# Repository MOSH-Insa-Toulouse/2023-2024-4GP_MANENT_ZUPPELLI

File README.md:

# 2023-2024-4GP_MANENT_ZUPPELLI
--- 
## Sommaire
   - [I) Contexte et objectifs du projet](#I-Contexteetobjectifsduprojet)
   - [II) Capteur à jauge de contrainte à base de crayon graphite](#II-Capteuràjaugedecontrainteàbasedecrayongraphite)
   - [III) Partie Analogique](#III-PartieAnalogique)
   - [IV) Code Arduino](#IV-CodeArduino)
   - [V) KiCad](#V-KiCad)
   - [VI) Banc de tests](#VI-Bancdetests)
   - [VII) Application mobile](#VII-Applicationmobile)
   - [VIII) Datasheet](#VIII-Datasheet)
     
---
  
## I) Contexte et objectifs du projet

L'objectif de ce projet est de réaliser un capteur low-tech à base de graphite. Les recherches ont démontré les nombreux avantages du carbone graphite. L’électronique à base de papier gagne en popularité parmi les ingénieurs grâce à sa facilité d’approvisionnement, sa simplicité de fabrication et son faible coût.<br>
Nous avons dû réaliser tous les processus de fabrication d'un shield PCB. Nous l'avons ensuite connecté à une plaque Arduino UNO.<br>
Notre shield contient 6 composants différents : une jauge de contrainte, un flex sensor, un écran oled, un encodeur rotatoire, un potentiomètre digital et un module Bluetooth.<br>
Par ailleurs, la carte Arduino fonctionne avec un code.<br>
Nous avons ensuite réalisé une application mobile connectée au module bluetooth.<br>
Nous avons évalué le capteur sur un banc de test.<br>
Puis nous avons fini par réaliser la datasheet du capteur de contrainte.<br>

## II)Capteur à jauge de contrainte à base de crayon graphite

Ce capteur low-tech utilise la théorie de la percolation au sein d’un système granulaire constitué de nanoparticules de graphite.<br>
Nous déposons une fine couche de graphite sur la feuille de papier ce qui présente un réseau percolé caractéristique. Dans ce réseau, le transport des électrons entre les nanoparticules est basé sur le mécanisme de l’effet tunnel.<br>
Lors de l'application d'une tension, le réseau percolé se trouve directement étendu. Cette déformation entraîne une augmentation de la distance effective entre les particules de graphite au sein du réseau. Une partie des chemins de percolation sont par conséquent rompus. Ainsi, la conduction du matériau diminue, donc la résistance de la couche de graphite augmente.<br>
Inversement, lors de l’application de déformations en compression, le réseau percolé se trouve directement comprimé. Cette déformation entraîne une diminution de la distance effective entre les particules.<br> Ainsi, de nouveaux chemins de percolation sont créés, la conduction du matériau augmente, soit la résistance de la couche de graphite diminue.

Une jauge de contrainte est un circuit résistif dont la résistance varie en fonction de sa déformation. Donc en mesurant les variations de résistance de la jauge, nous en avons déduit la contrainte et la déformation appliquées.<br>
Notre jauge de contrainte est alimentée par une tension régulée de 5V d'une carte Arduino UNO.
<br>
Ci-dessous, les 4 différentes jauges de contrainte que nous avons utilisé dans ce projet.

<p align="center">

<br>
<i>Capteur à jauge de contrainte à base de crayon graphite</i>
</p>

## III) Partie Analogique

Ce capteur graphite possède une résistance variable de l'ordre du GΩ. Le courant généré lorsque l'on applique une tension de 5V aux bornes du capteur est très faible.<br>
Pour obtenir un signal exploitable nous avons dû l'amplifier. Pour ce faire, nous avons utilisé un montage transimpédance constitué d'un amplificateur opérationnel.<br>
Pour cela nous avons dans un premier temps effectué une simulation électronique du capteur et de ce montage transimpédance sous LTSpice. Voici ci-dessous le montage réalisé sous LTSpice. Pour notre montage nous avons choisi l'AOP LTC1050 prenant en entrée un courant faible (de l'ordre d'une dizaine de picoampère).

<p align="center">

<br>
<i>Circuit amplificateur réalisé dans LTSpice</i>
</p>
<br>
Ce circuit amplificateur contient également 3 filtres passe bas passifs, dont nous avons pu tester le bon fonctionnement alternativement.<br>
<br>
- Le premier étage a une fréquence de coupure de 16 Hz, il permet de filtrer les bruits du courant en entrée. Nous avons testé ce premier étage pour vérifier que la fréquence de coupure soit la bonne.
<br>
</p>
<p align="center">

<br>
<i>Simulation de l'étage 1 dans LTSpice</i>
</p>
En effet la fréquence de coupure est la bonne.
<br>
- Le second étage a une fréquence de coupure de 1,6 Hz. Il permet de filtrer la composante de bruit du réseau électrique: le bruit à 50 Hz.
<br>
</p>
<p align="center">

<br>
<i>Simulation de l'étage 2 dans LTSpice</i>
</p>
En effet la fréquence de coupure est la bonne.
<br>
- Le dernier étage a une fréquence de coupure à 1,6 kHz qui permet d'atténuer le bruit provenant lors du traitement électronique.
<br>
</p>
<p align="center">

<br>
<i>Simulation de l'étage 3 dans LTSpice</i>
</p>
En effet la fréquence de coupure est la bonne.
<br> 
Conclusion : grâce à la simulation sur LTSpice, nous remarquons que notre signal de sortie atteindra les 1V, ce qui lui permet d'être récupéré et exploité par la carte arduino UNO.

## IV) Code Arduino

Le code Arduino permet la réception des mesures faites par les deux capteurs (Graphites et Flex Sensor) et d'afficher ces valeurs sur l'OLED. 
Notre programme principal est composé de sous programmes associés à ces éléments:
<br>
<p align="center">

<br>
<i>Capteur graphite</i>
<br>   
<p align="center">

<br>
<i>Flex Sensor</i>
<br>   
<p align="center">

<br>
<i>Ecran OLED</i>
<br>   
<p align="center">

<br>
<i>Encodeur rotatoire</i>
<br>   
<p align="center">

<br>
<i>Potentiomètre digital</i>
<br>   
<p align="center">

<br>
<i>Module Bluetooth</i>

## V) KiCad
Avant d'imprimer le PCB et de souder nos différents composants, nous avons dû dessiner les schémas électroniques, réaliser les composants électroniques et créer le PCB sur KICAD. Cette étape est importante car elle permet de prévisualiser le PCB, vérifier que tous les composants tiennent sur le PCB. Elle permet également de créer les différents routages de pistes.

<p align="center">

<br>
<i>Schémas électroniques</i>
</p>

<p align="center">

<br>
<i>Création du PCB et des différentes empreintes sur KiCad</i>
</p>

<p align="center">

<br>
<i>Visualisation 3D du PCB</i>
</p>
<br>
Une fois que nous avons été satisfaites de la disposition de nos différents composants électroniques, et du routage de pistes, nous avons pu imprimer le PCB, le percer et y souder les différents composants.
<br>
<br>
<p align="center">

<br>
<i>PCB terminé</i>
</p>

## VI) Banc de tests

Nous avons relevé la variation de résistance de notre capteur en fonction de son angle de déformation. Pour cela, nous avons fabriqué un banc de test avec des disques en papiers de rayons de courbure différents:
<br> 
<p align="center">

<br> 
<i>Banc de tests</i>
<br>

Nous avons réalisé les mesures pour une déformation du capteur en traction et en compression. Nous avons testé plusieurs crayons graphites qui ont des duretés différentes: 2H, 2B, HB, 6B. Les détails des calculs se trouvent sur le document nommé "bancdetest.xlsx"
<br>

Voici les résultats obtenus: 

<br>
<p align="center">

<br>
<i>graphique représentant la variation de résistance relative en fonction de la compression appliquée</i>
</p>
<br>

<br>
<p align="center">

<br>
<i>graphique représentant la variation de résistance relative en fonction de la tension appliquée</i>
</p>
<br>

Nous pouvons remarquer que les résistances des mines de crayon les plus tendres sont plus faibles que celles des mines les plus dures. En effet, les mines les plus tendres contiennent plus de particules de graphites, donc les traces de crayons paraissent plus foncées. Au contraire, les mines les plus dures contiennent moins de particules de graphites et plus de liants argileux donc elles paraissent les traces de crayons paraissent plus claires. Sous compression, les particules de graphites se rapprochent donc le courant circule plus facilement: la résistance diminue. A l'inverse, sous traction, les particules de graphites s'écartent ce qui facilite la déconnexion des voies de conduction donc le courant circule moins facilement: la résistance augmente.

## VII) Application mobile

Nous avons réalisé une application mobile sur le site MIT App Inventor. <br>
Une fois que le module bluetooth est connecté au téléphone, nous pouvons acquérir les données des capteurs en temps réel et les tracer sur le graphe. 

<br> 
<p align="center">

<br> 
<i>Face avant de l'application</i>
<br>

## VIII) Datasheet
<br> 
Nous avons déposé le PDF de la datasheet.

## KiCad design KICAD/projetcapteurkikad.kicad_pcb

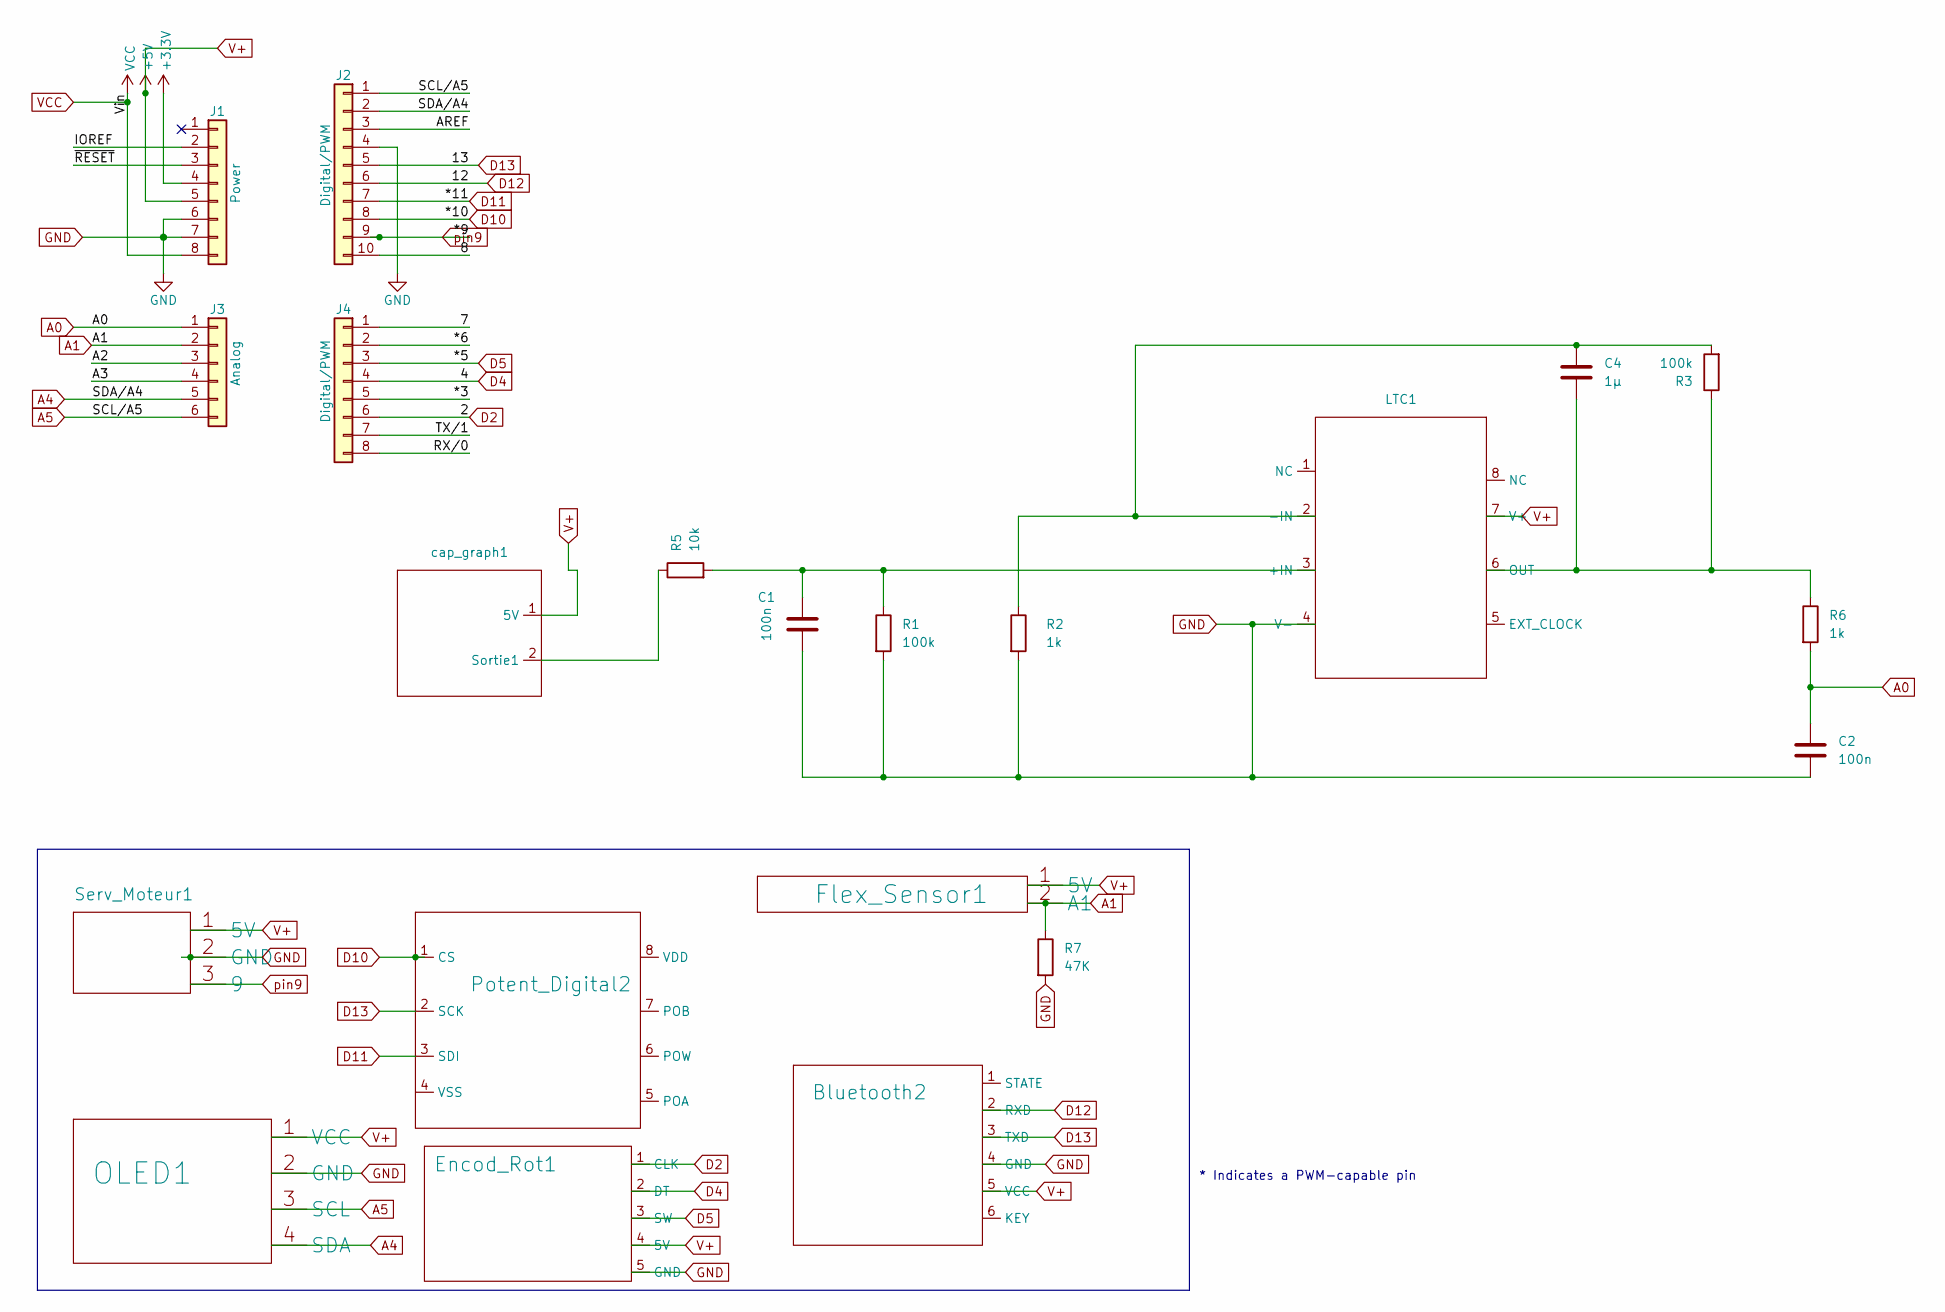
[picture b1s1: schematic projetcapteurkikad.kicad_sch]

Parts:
Bluetooth2: Bluetooth2
C1, C2: 100n; C_Axial_L3.8mm_D2.6mm_P7.50mm_Horizontal
C4: 1µ; C_Rect_L7.2mm_W3.5mm_P5.00mm_FKS2_FKP2_MKS2_MKP2
Encod_Rot1: Encod_Rot2
Flex_Sensor1: SIP-2
J1: Power; PinSocket_1x08_P2.54mm_Vertical
J2: Digital/PWM; PinSocket_1x10_P2.54mm_Vertical
J3: Analog; PinSocket_1x06_P2.54mm_Vertical
J4: Digital/PWM; PinSocket_1x08_P2.54mm_Vertical
LTC1: LTC1050
OLED1: OLED_new
Potent_Digital2: Potentiometre_Digital3
R1, R3: 100k; R_Axial_DIN0207_L6.3mm_D2.5mm_P5.08mm_Vertical
R2, R6: 1k; R_Axial_DIN0207_L6.3mm_D2.5mm_P5.08mm_Vertical
R5: 10k; R_Axial_DIN0207_L6.3mm_D2.5mm_P5.08mm_Vertical
R7: 47K; R_Axial_DIN0207_L6.3mm_D2.5mm_P5.08mm_Vertical
Serv_Moteur1: Servomoteur
cap_graph1: capp_graph

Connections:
+3V3: J1.4
/7: J4.1
/8: J2.10
/*3: J4.5
/*6: J4.2
/A2: J3.3
/A3: J3.4
/AREF: J2.3
/IOREF: J1.2
/RX/0: J4.8
/TX/1: J4.7
/~RESET: J1.3
A0: C2.1, J3.1, R6.2
A1: Flex_Sensor1.2 (A1), J3.2, R7.1
A4: J2.2, J3.5, OLED1.4 (SDA)
A5: J2.1, J3.6, OLED1.3 (SCL)
D2: Encod_Rot1.1 (CLK), J4.6
D4: Encod_Rot1.2 (DT), J4.4
D5: Encod_Rot1.3 (SW), J4.3
D10: J2.8, Potent_Digital2.1 (CS)
D11: J2.7, Potent_Digital2.3 (SDI)
D12: Bluetooth2.2 (RXD), J2.6
D13: Bluetooth2.3 (TXD), J2.5, Potent_Digital2.2 (SCK)
GND: Bluetooth2.4 (GND), C1.2, C2.2, Encod_Rot1.5 (GND), J1.6, J1.7, J2.4, LTC1.4 (V-), OLED1.2 (GND), R1.2, R2.2, R7.2, Serv_Moteur1.2 (GND)
unnamed: C1.1, LTC1.3 (+IN), R1.1, R5.2
unnamed: C4.1, LTC1.2 (-IN), R2.1, R3.2
unnamed: C4.2, LTC1.6 (OUT), R3.1, R6.1
unnamed: R5.1, cap_graph1.2 (Sortie1)
V+: Bluetooth2.5 (VCC), Encod_Rot1.4 (5V), Flex_Sensor1.1 (5V), J1.5, LTC1.7 (V+), OLED1.1 (VCC), Serv_Moteur1.1 (5V), cap_graph1.1 (5V)
VCC: J1.8
pin9: J2.9, Serv_Moteur1.3 (9)

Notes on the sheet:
* Indicates a PWM-capable pin

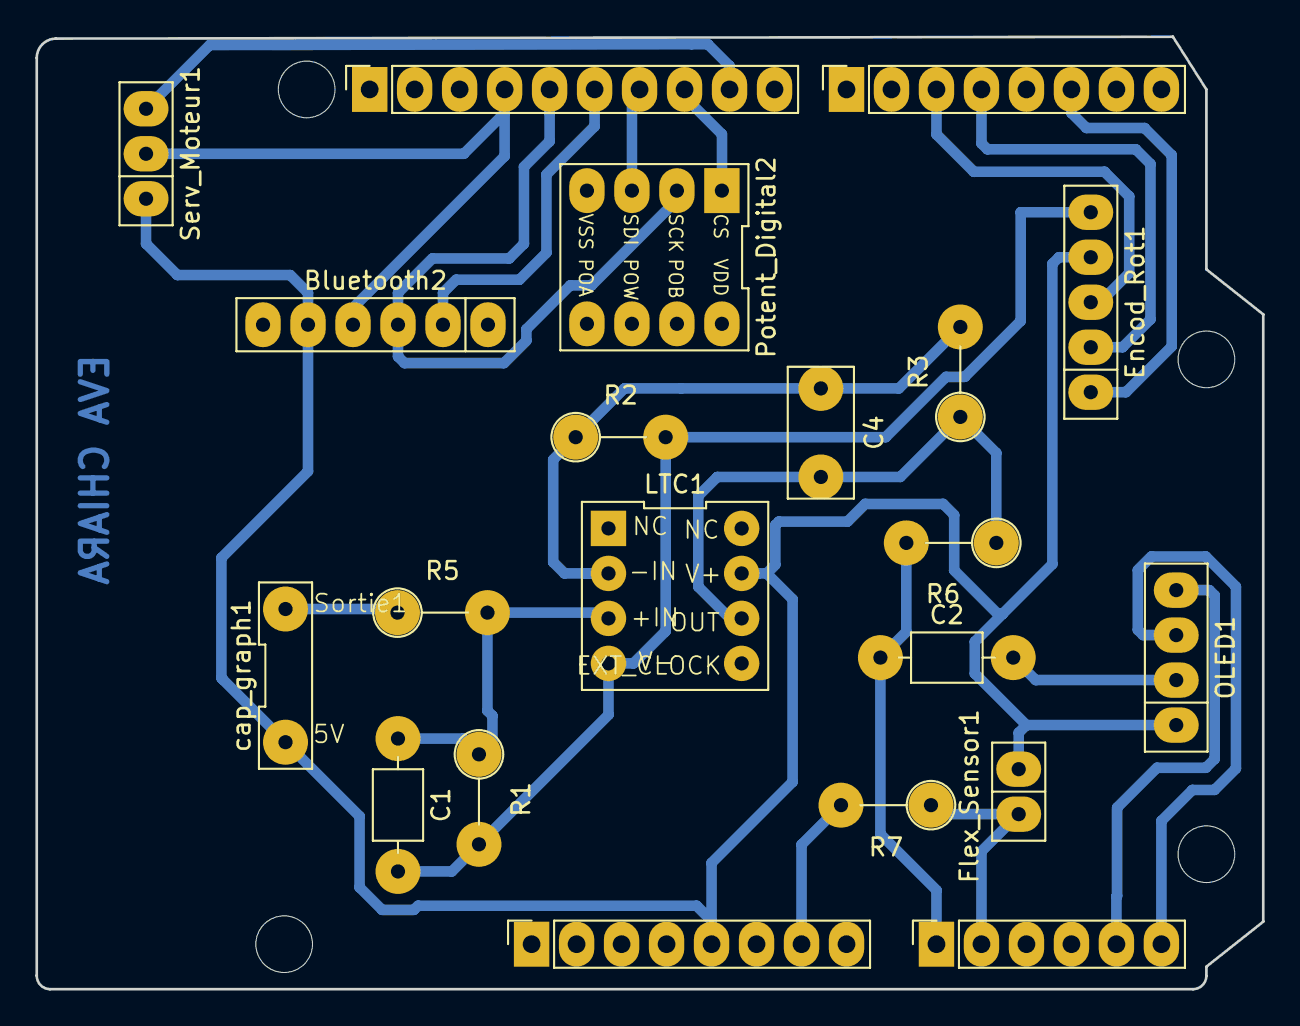
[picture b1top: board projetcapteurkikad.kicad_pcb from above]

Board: 2 copper layers, 69.2 x 53.8 mm, 25 parts (0 on the bottom side), 18 nets.

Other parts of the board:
MH1, MH2, MH3, MH4: MountingHole_3.2mm

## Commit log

2024-05-31 Create kicad
